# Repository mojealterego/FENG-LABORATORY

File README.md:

# FENG-LABORATORY — Thermo-IoT

**OCHRONA WYNALAZKU:** Repozytorium jest **publiczne**, a wcześniejsze commity mogą stanowić ujawnienie stanu techniki. Copyright ani dopisek „All rights reserved” **nie zastępuje zgłoszenia patentowego**. Nie publikować nowych unikatowych rozwiązań konstrukcyjnych przed przeglądem przez rzecznika patentowego. [Procedura IP](docs/IP_PROTECTION_PL.md) · [Rejestr dat publicznych ujawnień](docs/IP_PUBLIC_DISCLOSURE_REGISTER.md).

**Prawa autorskie i kontakt:** © 2026 **Mojeaterego — Andrzej Mikulski**. **Wszelkie prawa zastrzeżone / All rights reserved.** E-mail: **mojealterego21@gmail.com** · tel. **+48 455 575 337**. Szczegóły: [LICENSE](LICENSE).

Repozytorium rozwojowe projektu **Thermo-IoT** w kontekście FENG 2.27 „Laboratorium Innowatora”.

**Stan na 9 października 2026:** zweryfikowany kod referencyjny, testy i dokumentacja koncepcyjna. **Brak potwierdzonego prototypu, eksperymentów metrologicznych i poziomu TRL.** Ani dostęp do programu, ani dofinansowanie nie są zagwarantowane.

## Dostarczone podsystemy

| Moduł | Zakres | Czego nie dowodzi |
|---|---|---|
| `thermo_iot.energy` | energia superkondensatora, bilans mocy netto, limit duty cycle | mocy na konkretnej rurze |
| `thermo_iot.scheduler` | interwał pomiarowy, rezerwa i ograniczenia mocy | szczytowego prądu TX i cold start |
| `thermo_iot.telemetry` | wersjonowany protokół 8 B, parser TTN v3, idempotentna baza SQLite | pracy LoRaWAN na urządzeniu |
| `thermo_iot.gateway` | offline ingest / report, lokalny webhook z tokenem | bezpiecznej publicznej usługi produkcyjnej |
| `thermo_iot.anomaly` | odporna statystyka odchyleń temperatury | wykrycia wycieków i błędów procesowych |
| `thermo_iot.lab` | analiza pomiarów I–V/TEG z jawnie oznaczonym źródłem danych | kalibracji i jakości pomiarów |
| `firmware/` | przenośny kodek C11 testowany z Pythonem | kompletnego firmware, PCB i modemu |

## Uruchomienie (Python 3.10+ / C11)

```bash
python -m unittest discover -s tests -v
python -m thermo_iot --teg-mw 0.1 --efficiency 0.65 --sleep-uw 8 --cycle-mj 21.9
python -m thermo_iot.gateway ingest --db local-telemetry.sqlite --file examples/ttn_v3_uplink.json
python -m thermo_iot.gateway report --db local-telemetry.sqlite --app district-heat --device pipe-1
python -m thermo_iot.lab --file examples/synthetic_teg_sweep.csv
cc -std=c11 -Wall -Wextra -Werror -pedantic -Ifirmware/include firmware/src/thermo_iot_frame.c firmware/tests/test_frame.c -o /tmp/thermo-iot-frame-tests
/tmp/thermo-iot-frame-tests
```

**Ostrzeżenie: przyklad --cycle-mj 21.9 nie jest zweryfikowaną energią cyklu LoRaWAN.** Wyłącznie ilustracyjny impuls 87 mA x 200 ms przy 3,3 V pobiera ponad 57 mJ przed oknami RX i stratami. PCB ma tylko C6=470 uF na VOUT, co stanowi elektryczny HOLD/NO-GO dla referencyjnego profilu. Symulowane 2,5 F nie istnieje na tej szynie, a VSTORE 5,25 V nie wolno podłączać bezpośrednio do STM32WLE. Analizy: [power_gate](thermo_iot/power_gate.py), [harvester_rail](thermo_iot/harvester_rail.py) i [protokół](docs/RF_POWER_BROWNOUT_HOLD.md). Nie są to pomiary fizyczne.

**Uwaga:** w plikach przykładowych występują wyłącznie **syntetyczne** dane przeznaczone do demonstracji formatu. Lokalny webhook wymaga tokenu i nie jest wystawiany domyślnie poza localhost. Zob. [protokół IoT](docs/PROTOKOL_IOT.md).

## Demonstrator panelu telemetrii (lokalnie)

```bash
python -m thermo_iot.demo --db ./thermo-synthetic-demo.sqlite --count 144
python -m thermo_iot.dashboard --db ./thermo-synthetic-demo.sqlite --port 8766
```

Otwórz `http://127.0.0.1:8766/` na komputerze, na którym działa Python. Dane są **wygenerowane syntetycznie** i zapisywane wyłącznie do nowo utworzonej bazy; skrypt odmawia nadpisania istniejącej bazy. Panel nie pozwala na sterowanie instalacją ani jej urządzeniami. [Opis dashboardu](docs/DASHBOARD.md).

## Baza dokumentacji

- [Karta robocza do wniosku IPB](docs/WNIOSEK_THERMO_IOT.md)
- [Audyt twierdzeń i ryzyk](docs/AUDYT_TWIERDZEN.md)
- [Plan walidacji i progi GO/NO-GO](docs/PLAN_WALIDACJI.md)
- [Model biznesowy i walidacja klientów](docs/MODEL_BIZNESOWY.md)
- [Źródła formalne i naukowe](docs/ZRODLA.md)
- [Architektura MVP](docs/ARCHITEKTURA_MVP.md)
- [Protokół telemetrii / TTN](docs/PROTOKOL_IOT.md)
- [Zasady oceny analityki](docs/ANALITYKA.md)
- [Protokół metrologii TEG i analizy CSV](docs/METROLOGIA_TEG.md)
- [Analiza konkurencji i wcześniejszego stanu techniki](docs/PRIOR_ART_I_WYROZNIK.md)
- [Lista kontrolna gotowości zgłoszenia](docs/GOTOWOSC_ZGLOSZENIA.md)
- [Harmonogram 12 tygodni](docs/HARMONOGRAM_12_TYGODNI.md)
- [BOM funkcjonalny i wymagania techniczne](docs/BOM_I_WYMAGANIA_TECHNICZNE.md)
- [Przegląd kandydatów PMIC/MCU/sensora i ryzyk rozruchu](docs/HARDWARE_PRELIMINARY.md)
- [Energia z profilu czasowego generatora](docs/TRACE_SIMULATION.md)
- [Firmware: histereza i bramka mocy](docs/FIRMWARE_POWER_POLICY.md)
- [Granice bezpieczeństwa IT/OT](SECURITY.md)

## Faza HW / Firmware / Walidacja LoRaWAN (2026-10-09)

**Implementacje repozytoryjne są przeznaczone do prób laboratoryjnych — brak dowodu fizycznej integracji.** Zobacz [macierz stanu dowodowego](docs/STATUS_HARDWARE_TESTS.md).

- [KiCad — schemat i PCB pasywnego adaptera stanowiska](hardware/kicad/) (nie jest finalną płytą PMIC/MCU ani wydanym Gerberem).
- [STM32WLE5JC — aplikacja C11 i wymagany adapter CubeWL](docs/STM32WLE5_FIRMWARE.md) (laboratoryjny ELF/HEX z GNU ARM GCC dostępny z CI; niewgrany do fizycznego MCU).
- [Wio-E5: sprzętowy test jednej transmisji i weryfikacja odczytu TTN](docs/TEST_LORAWAN_REAL.md) (wymaga rzeczywistego urządzenia).
- [TEG i PMIC — akwizycja SCPI oraz metrologia](docs/TEG_PMIC_CAPTURE.md) (bez pomiarów rzeczywistych w repo).

Przykładowy test kontrolny portu, **bez emisji**:

```bash
python -m pip install pyserial
python -m thermo_iot.lorawan_fieldtest --port COM3
```

Pojedynczy test fizycznego nadawania (tylko po skonfigurowaniu OTAA/anteny i sprawdzeniu lokalnych wymogów radiowych):

```bash
python -m thermo_iot.lorawan_fieldtest --port COM3 --send --temperature-centic 4300 --capacitor-mv 3000
```

COM3 jest tylko przykładem Windows i musi zostać zastąpiony faktycznym portem. Liczby w tym teście są wpisywane przez operatora; nie dowodzą pracy czujnika. Odbiór należy oddzielnie potwierdzić w The Things Stack.

## Projekt aktywnego harvester'a i ścieżka weryfikacji fizycznej — październik 2026

**Nowe elementy przeznaczone do rzeczywistej budowy demonstratora:**

- [LTC3108GN16 — schemat aktywnego PMIC i projekt PCB w KiCad](hardware/active_power/) — PCB **częściowo trasowana: 2 nets połączone, 28 pozycji nadal niepołączonych**, status produkcyjny HOLD; transformator 1:100 poza płytką.
- [Natywny overlay STM32CubeIDE dla STM32WLE5JC / Wio-E5](firmware/stm32wle5jc/README.md) — generator 4 plików integrowanych z oficjalnym Seeed LoRaWAN End Node; **zbudowano ELF/HEX dla profilu laboratoryjnego; brak flash urządzenia**.
- [Pobieranie rzeczywistych parametrów PMIC z pięciu przyrządów SCPI](thermo_iot/pmic.py) — wejście, wyjście, VSTORE, próba cold-start (wymaga własnej aparatury).
- [Próba radiowa Wio-E5 EU868 i weryfikacja odczytu TTN](thermo_iot/lorawan_fieldtest.py) — program istnieje, **brak rzeczywistego raportu odbioru**.
- [Aktualna macierz GO/NO-GO dla sprzętowego MVP](docs/STATUS_HARDWARE_TESTS.md).

**Uwaga:** bit 7 ramki LoRaWAN (0x80) oznacza laboratoryjny odczyt temperatury wewnętrznej MCU. Backend przechowuje te rekordy jako `reference_telemetry` i **wyklucza je z wykrywania anomalii rurociągu**. Nie wolno przedstawiać ich jako pomiaru rury lub wycieku.

## Kamień milowy: pełny build referencyjnego firmware STM32WLE5JCIx

**Weryfikacja 9.10.2026:** w GitHub Actions rzeczywiście skompilowano i zlinkowano natywny obraz **ELF/Intel HEX**, ze startup i linker script producenta Seeed, na `arm-none-eabi-gcc`. Dane kompilacji: **63 564 B FLASH (24,25% z 256 KiB)**, **8 068 B BSS** i **228 B DATA**. SHA-256 HEX: `e9a3d1df50e8c5a0eb3a52d03a78ce236c72ead47e3924e0c9d1b1b63d66a4ea`.

[GitHub Actions: udany pełny build ELF/HEX](https://github.com/mojealterego/FENG-LABORATORY/actions/runs/37956017016) · [archiwum ELF/HEX/MAP](https://github.com/mojealterego/FENG-LABORATORY/actions/runs/37956017016/artifacts/11627633166) · [skrypt kompilacji](firmware/stm32wle5jc/build_cube_gcc.py).

**Granica dowodowa:** jest to kompletna kompilacja **referencyjnego firmware LoRaWAN RF** (temperatura krzemu STM32, ręcznie brak TEG/supercap), a **nie docelowy pełny firmware bezbateryjnego czujnika rury**. Nie nastąpiło programowanie układu SWD, OTAA w środowisku fizycznym, pomiar TX ani odbiór w TTN.

## Ocena jakości uplinków LoRaWAN — tylko analiza lokalnego eksportu TTN

Nowy moduł [`thermo_iot.rf_audit`](docs/RF_FIELD_AUDIT.md) weryfikuje plik JSONL z faktycznie wyeksportowanymi (przez operatora) zdarzeniami The Things Stack v3. Zlicza unikatowe ramki, ponowne dostarczenia, zmiany sesji, nieciągłości FCnt i dostępne RSSI/SNR; izoluje laboratoryjne ramki 0x80 od danych czujnika rury. **Nie wylicza „procentu dostarczonych pakietów” z samych odebranych ramek**, ponieważ nie znamy wszystkich prób nadawania.

```bash
python -m thermo_iot.rf_audit --file private/mvp-evidence/ttn-uplinks.jsonl \
  --app-id thermo-lab --device-id pipe-1
```

Plik JSONL ma być zachowany wyłącznie lokalnie/prywatnie, bez tokenów, kluczy ani nieujawnionych rozwiązań patentowych. Analiza samego eksportu nie poświadcza, że użytkownik przeprowadził transmisje.

## Prywatne dowody fizycznego MVP (poza GitHub)

Moduł `thermo_iot.mvp_acceptance` analizuje w **prywatnym katalogu** kompletność, SHA-256 i spójność 7 typów dokumentów: TEG I-V, PMIC cold-start, raport z UART, niezależny uplink TTN, wynik DRC **aktywnego** PCB, log flash MCU i zapis 7 dni pracy energetycznej. **Nie nadaje automatycznie statusu „fizyczne MVP wykonane”.**

```bash
python -m thermo_iot.mvp_acceptance --root private/mvp-evidence --create-manifest
python -m thermo_iot.mvp_acceptance --root private/mvp-evidence
```

Wymaga **wcześniej faktycznie wykonanych pomiarów i zdarzeń**; nie generuje fałszywych danych. [Procedura i kryteria](docs/MVP_EVIDENCE_PRIVATE.md). Ścieżka `private/` jest ignorowana przez Git i blokowana przez lokalne hooki przed publikacją.

## Krytyczny warunek zasilania impulsowego LoRaWAN

W publicznym projekcie LTC3108 zamontowany kondensator C6 = **470 µF** stanowi **elektryczny NO-GO** dla przyjętego profilu 87 mA przez 200 ms, nawet z optymistycznym 4,5 mA wsparciem PMIC. Referencyjne wyliczenie pierwszego rzędu wskazuje minimum ~**13,1 mF** bez zapasu temperaturowego/tolerancji. Zasilenie STM32 bezpośrednio z VSTORE ~5,25 V jest niedopuszczalne. [Szczegółowa analiza](docs/RF_POWER_BROWNOUT_HOLD.md). To wynik symulacji, nie pomiar. Aktywna PCB i fizyczne MVP pozostają **HOLD**.

## Warunki przed zgłoszeniem

Wymagane są potwierdzone dane pomysłodawców, właścicieli praw IP, zasoby, kompetencje, oświadczenia formalne i oryginalny formularz operatora. Kod i wyniki symulacji nie mogą zastępować protokołów zbudowania i walidacji urządzenia.

Zalecana kolejność: **pomiar TEG → bilans energetyczny/PMIC → podzespoły i prototyp → telemetryka terenowa → zbiór zdarzeń → model predykcyjny → biznes/SLA**.

Prace prowadzone w gałęzi `main`, testowane automatycznie przez GitHub Actions.

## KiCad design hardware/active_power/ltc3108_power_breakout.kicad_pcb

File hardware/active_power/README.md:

# Active Thermo-IoT harvester PCB candidate A0 (LTC3108GN16)

## Important status

This folder contains **native KiCad schematic/net-assigned PCB for an LTC3108 active power breakout**, not a finalized complete industrial IoT device. The PCB has placed parts, assigned nets, and **two explicitly routed charge-pump connections** (C1.2→U1.13, C2.2→U1.14); the remainder is still UNROUTED. Real KiCad 10 automated ERC/DRC has been RUN, but **blocking warnings and unconnected copper remain**; there is no passed manufacturing signoff, mechanical clearance/assembly validation, or hot/cold-start test. **Do NOT send to PCB fabrication as is.**

The design uses the **LTC3108EGN** 16-pin SSOP package and an **external transformer** for ease of bench swapping. Pin numbering matches the manufacturer GN16 top-view drawing (Rev D). Manufacturer typical application: https://www.analog.com/media/en/technical-documentation/data-sheets/3108fc.pdf.

## Architecture and rationale

J1 TEG source -> C5 reservoir + primary of external 1:100 transformer (J2 primary TEG_P to SW). Secondary ground/Sec_HI -> C1 1nF and C2 330pF -> LTC3108's C1/C2 charge pump. VS1=VAUX and VS2=GND selects **3.3V** VOUT. C3 1uF VAUX, C4 2.2uF VLDO. J3 exposes VOUT with C6 470uF. J4 exposes 5V VSTORE for an external 0.1F / 6.3V energy reservoir (C7 DNP). J5 exposes PGD for a **high-impedance** diagnostic probe. VOUT2_EN tied to GND, VOUT2 unused.

**Critical:** J2 four-pin 2.54mm transformer breakout does not correspond to the transformer manufacturer's surface-mount pad numbering. Confirm coil polarity/pinout and orientation on the real LPR6235 before assembly; no transformer is soldered on this PCB.

| IC pin | Function | Circuit net |
|---|---|---|
| 1, 8, 9, 16 | GND | GND |
| 2 | VAUX | VAUX |
| 3 | VSTORE | VSTORE |
| 4 | VOUT | VOUT |
| 5 | VOUT2 | NC_VOUT2 / unconnected |
| 6 | VLDO | VLDO |
| 7 | PGD | PGD |
| 10 | VS2 | GND |
| 11 | VS1 | VAUX |
| 12 | VOUT2_EN | GND |
| 13 | C1 | PMIC_C1 |
| 14 | C2 | PMIC_C2 |
| 15 | SW | SW |

## Stop/go constraints

* **Minimum 20mV** LTC3108 startup is datasheet input voltage under a 1:100 transformer, NOT a claim about any particular TEG, output current, zero gradient or autonomous 87mA radio peaks.
* LTC3108 VOUT current limit from datasheet ~2.8–7.5 mA (typ ~4.5mA), far below potential LoRa high-power pulses; **supply RF from measured reservoir energy**, and implement supervised power gating, hold-up / ESR tests, and output supply-current limits.
* VSTORE operates at about 5 V, **not acceptable as direct STM32WLE supply**. Connect MCU only to verified VOUT 3.3 V rail (and review startup/sag).
* The selected capacitor footprints / dimensions are *placeholders*, not approved mechanical data. Choose actual vendor MPNs, tolerances, lead pitch, ESR and leakage, and recalculate hold-up before routing.
* Avoid connecting J1 to live district heating conductors, mains, or unqualified hot surfaces. All measurements must be done on a controlled isolated low-voltage thermal rig.

## Required remaining manufacturing gates

1. Exact BOM manufacturers, cap lead pitch, Coilcraft winding pin mapping, safe VS1 selection and TEG voltage/current envelope verified.
2. KiCad opens schematic and PCB and reports **zero blocking ERC/DRC**, zero unconnected nets after a proper manual route, correct pad/net parity, mask clearance and track capacity.
3. Independent review of thermal, electrical and RF wiring and source mechanical drawings.
4. Gerber + Excellon drill exports and independent preview; then limited prototype fabrication with current-limited bench bring-up.
5. Cold-start, brownout, leakage, ESR and peak TX/RX validation. No claims of measured performance until archived data exists.

## Footprint source library

The local `ThermoActive.pretty/` directory and `fp-lib-table` resolve the custom SMD/TH footprints used in the schematic. They are **engineering placeholders**, not manufacturer-validated land patterns. In particular, `RadialCap` stands for an unselected 2.54mm-pitch THT cap and can be dangerous if a larger diameter, different polarity, clearance or thermal derating is required. The SSOP16 land-pattern is provisional and must be compared with Analog Devices GN16 recommended solder pattern before release.

## Routing progress — 9 Oct 2026 (A0 candidate; NOT FOR FAB)

The **manufacturer-reference** capacitor-to-LTC3108 nets `PMIC_C1` and `PMIC_C2` have now been laid on F.Cu at 0.20 mm nominal width. The real KiCad 10.0.6 DRC diagnostics [37960523837](https://github.com/mojealterego/FENG-LABORATORY/actions/runs/37960523837) report **28 unconnected pads remaining**, down from 30, and **13 existing footprint-library mismatch warnings**. There were no new inter-track violations reported for the two routed nets. These are preliminary reference-board traces, **not an undisclosed novel circuit**. Transformer pin order, capacitor land-patterns, ESR, clearance, and all other wiring remain HOLD; the board shall not be manufactured or attached to live heating infrastructure without independent electrical/DFM validation.

`hardware/cad_gate.py` interprets KiCad textual DRC to machine-readable `HOLD` / `ENGINEERING_REVIEW_REQUIRED`. Even a hypothetical zero-violation DRC result never sets `fabrication_authorized` to true — a human review is mandatory.

## Explicit RF supply brownout blocker (electrical engineering HOLD)

The open C6 = **470 µF at VOUT 3.3 V** is not sufficient as the sole storage capacitor for the **illustrative** 87 mA / 200 ms STM32WLE transmit pulse even under the optimistic constant LTC3108 VOUT current assumption. A charge/ESR first-order model suggests at least **13.1 mF** for the specified illustrative pulse and minimum voltage, before derating and protection margins. This number is **NOT** a production capacitor selection or a validated performance value. VSTORE (nominally around 5 V) must never be directly connected to STM32WLE VDD. Independent current transient measurement and a suitable qualified power architecture remain prerequisites.

See [reproducible power-integrity analysis](../../docs/RF_POWER_BROWNOUT_HOLD.md) and `python -m thermo_iot.harvester_rail`. Engineering status remains **HOLD** even if routing progress reduces unconnected pads.

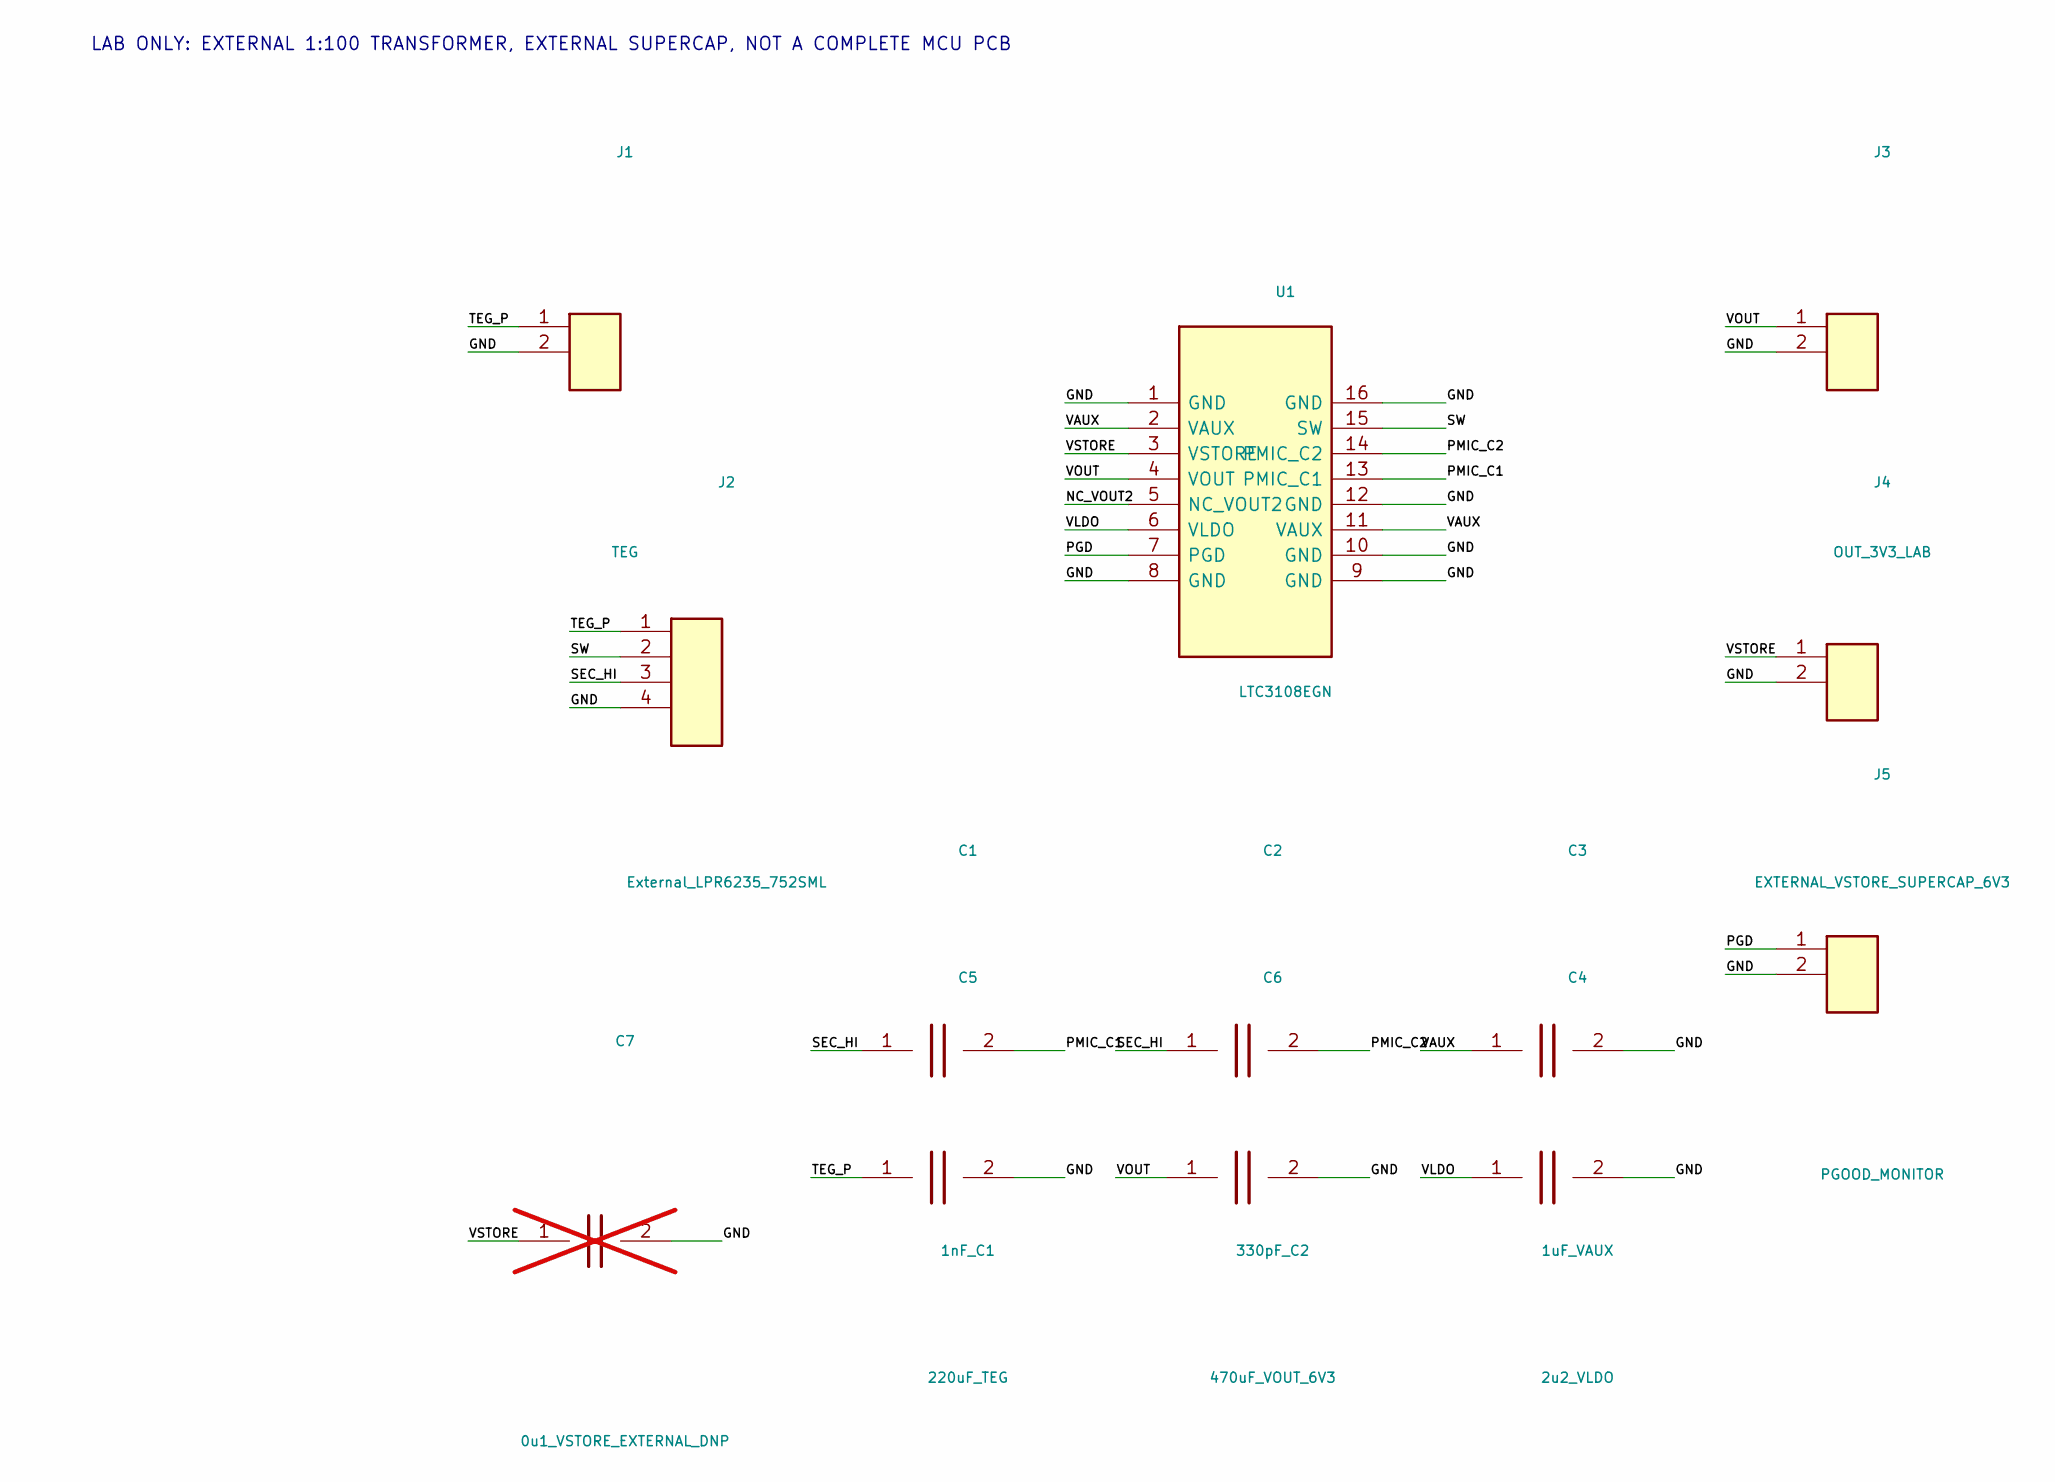
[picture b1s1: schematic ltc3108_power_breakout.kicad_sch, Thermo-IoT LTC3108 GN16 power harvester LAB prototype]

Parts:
C1: 1nF_C1; Cap0805
C2: 330pF_C2; Cap0805
C3: 1uF_VAUX; Cap0805
C4: 2u2_VLDO; Cap0805
C5: 220uF_TEG; RadialCap
C6: 470uF_VOUT_6V3; RadialCap
C7: 0u1_VSTORE_EXTERNAL_DNP; RadialCap; not fitted
J1: TEG; Header1x2
J2: External_LPR6235_752SML; Header1x4
J3: OUT_3V3_LAB; Header1x2
J4: EXTERNAL_VSTORE_SUPERCAP_6V3; Header1x2
J5: PGOOD_MONITOR; Header1x2
U1: LTC3108EGN; SSOP16_P0635

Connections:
GND: C3.2, C4.2, C5.2, C6.2, C7.2, J1.2, J2.4, J3.2, J4.2, J5.2, U1.1 (GND), U1.8 (GND), U1.9 (GND), U1.10 (GND), U1.12 (GND), U1.16 (GND)
NC_VOUT2: U1.5 (NC_VOUT2)
PGD: J5.1, U1.7 (PGD)
PMIC_C1: C1.2, U1.13 (PMIC_C1)
PMIC_C2: C2.2, U1.14 (PMIC_C2)
SEC_HI: C1.1, C2.1, J2.3
SW: J2.2, U1.15 (SW)
TEG_P: C5.1, J1.1, J2.1
VAUX: C3.1, U1.2 (VAUX), U1.11 (VAUX)
VLDO: C4.1, U1.6 (VLDO)
VOUT: C6.1, J3.1, U1.4 (VOUT)
VSTORE: C7.1, J4.1, U1.3 (VSTORE)

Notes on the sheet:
LAB ONLY: EXTERNAL 1:100 TRANSFORMER, EXTERNAL SUPERCAP, NOT A COMPLETE MCU PCB

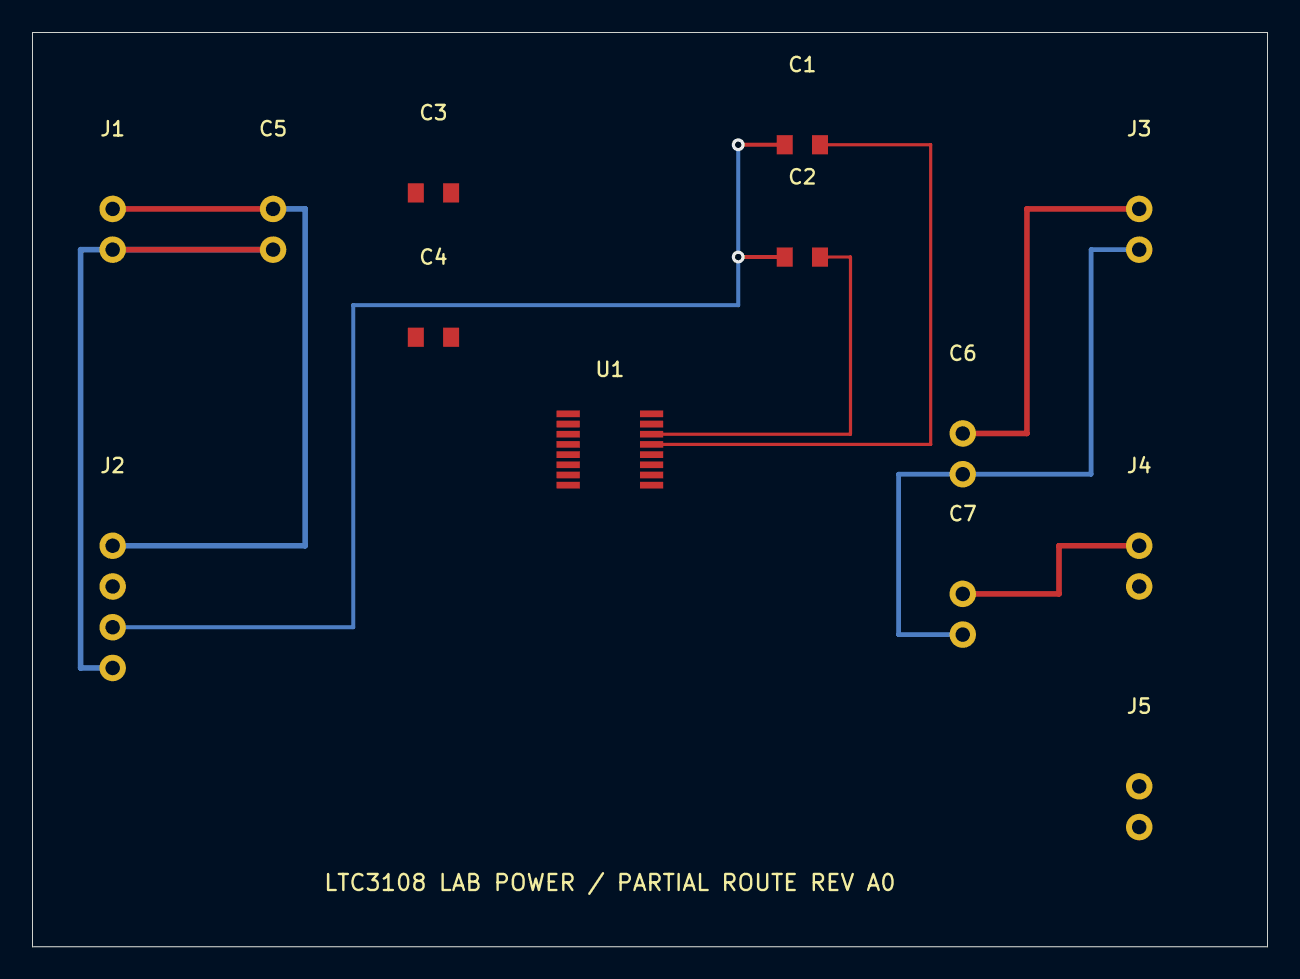
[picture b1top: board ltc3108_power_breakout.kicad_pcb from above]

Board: 2 copper layers, 77.0 x 57.0 mm, 13 parts (0 on the bottom side), 11 nets.

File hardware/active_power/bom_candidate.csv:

Ref,Component,Value/Specification,Footprint,Notes
U1,LTC3108EGN,LTC3108 SSOP16 GN,ThermoActive:SSOP16_P0635,Manufacturer pinout Rev D verify before assembly
C1,Ceramic,1nF >=10V,ThermoActive:Cap0805,C1 coupling
C2,Ceramic,330pF >=16V,ThermoActive:Cap0805,C2 coupling
C3,Ceramic,1uF >=6.3V,ThermoActive:Cap0805,VAUX decoupling
C4,Ceramic,2.2uF >=6.3V,ThermoActive:Cap0805,VLDO decoupling
C5,Polarized input reservoir,220uF low leakage >=6.3V,ThermoActive:RadialCap,Verify leakage and actual lead pitch
C6,Polarized regulated output,470uF >=6.3V low ESR,ThermoActive:RadialCap,Check ripple and pulses
C7,DNP optional VSTORE,DNP,ThermoActive:RadialCap,External supercap on J4 instead
J1,TEG terminal,2-pin 2.54mm,ThermoActive:Header1x2,TEG_P and GND
J2,External transformer connector,4-pin 2.54mm,ThermoActive:Header1x4,Winding polarity requires verification with Coilcraft
J3,Output 3.3V terminal,2-pin 2.54mm,ThermoActive:Header1x2,Do not attach MCU until safe load profiling
J4,External 0.1F 6.3V supercap,2-pin 2.54mm,ThermoActive:Header1x2,Check ESR leakage polarity max ratings
J5,PGOOD monitor,2-pin 2.54mm,ThermoActive:Header1x2,High impedance meter only
T1,Transformer external,Coilcraft LPR6235-752SML 1:100,NOT ON PCB,Needs physical breakout and winding verification

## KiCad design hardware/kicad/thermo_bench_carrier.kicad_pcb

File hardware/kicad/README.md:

# Thermo-IoT Bench Carrier A0 — native KiCad sources

**Funkcja:** pasywna, dwuwarstwowa płytka *stanowiska laboratoryjnego*, nie docelowy system bezbateryjny i nie płytka z układem LTC3108. Służy do podłączenia zewnętrznie zasilanej płytki Wio-E5, UART USB (3,3 V), toru pomiarowego surowego TEG i oddzielnego pomiaru PMIC.

## Złącza (pad nr 1 wyznacza pad prostokątny)

| Ref | Pad | Net | Cel |
|---|---|---|---|
| J1 | 1,2 | `+3V3_EXT`, `GND` | **tylko laboratoryjny** regulowany zasilacz 3,3 V, ograniczenie prądu |
| J2 | 1..4 | `+3V3_EXT`, `GND`, `MCU_TX`, `MCU_RX` | interfejs Wio-E5 Dev Board (sprawdzić ręcznie pinout przed podłączeniem) |
| J3 | 1..3 | `GND`, `MCU_RX`, `MCU_TX` | konwerter USB-UART logic 3,3 V; RX adaptera -> J2.3, TX -> J2.4 |
| J4 | 1,2 | `TEG_P`, `TEG_N` | wyłącznie pomiar TEG, brak połączenia z obwodami zasilania |
| J5 | 1,2 | `PMIC_VOUT`, `PMIC_RETURN` | wyłącznie pomiar PMIC, brak połączenia z Wio-E5 i J1 |

**OSTRZEŻENIE:** Nie wolno bezpośrednio łączyć 5 V VSTORE LTC3108, jego 2,2 V wyjścia LDO albo niestabilnego napięcia z TEG z pinami MCU. Płytka nie zawiera ogranicznika przepięć, bezpiecznika ani regulatora. Traktować ją jako **przyrząd laboratoryjny do niskich napięć** i zasilać J1 z zabezpieczonego zasilacza 3,3 V; nie instalować na pracującej instalacji przemysłowej.

## Pliki

- `thermo_bench_carrier.kicad_sch`: schemat z 5 złączami i identycznymi nazwami nets.
- `thermo_bench_carrier.kicad_pcb`: dwuwarstwowa PCB z trasami tylko dla zasilania UART+3.3 V/GND, TEG i PMIC są **osobnymi, niepołączonymi parzystymi złączami pomiarowymi**.
- `ThermoBench.pretty/`: wbudowane źródła footprintów 1×2, 1×3, 1×4, raster 2,54 mm.
- `fp-lib-table`: lokalna biblioteka footprintów.

Płytka ma **70 × 44 mm** (obrys x=12..82; y=13..57), przewierty padów 1,0 mm. Przed zamówieniem PCB wymaga weryfikacji w **KiCad ERC/DRC, orientacji pinów, tolerancji mechanicznych i przeglądu DFM**. To nie jest produkcyjnie zweryfikowany Gerber — w repo nie ma autoryzowanego testu sprzętowego ani walidacji EDA.

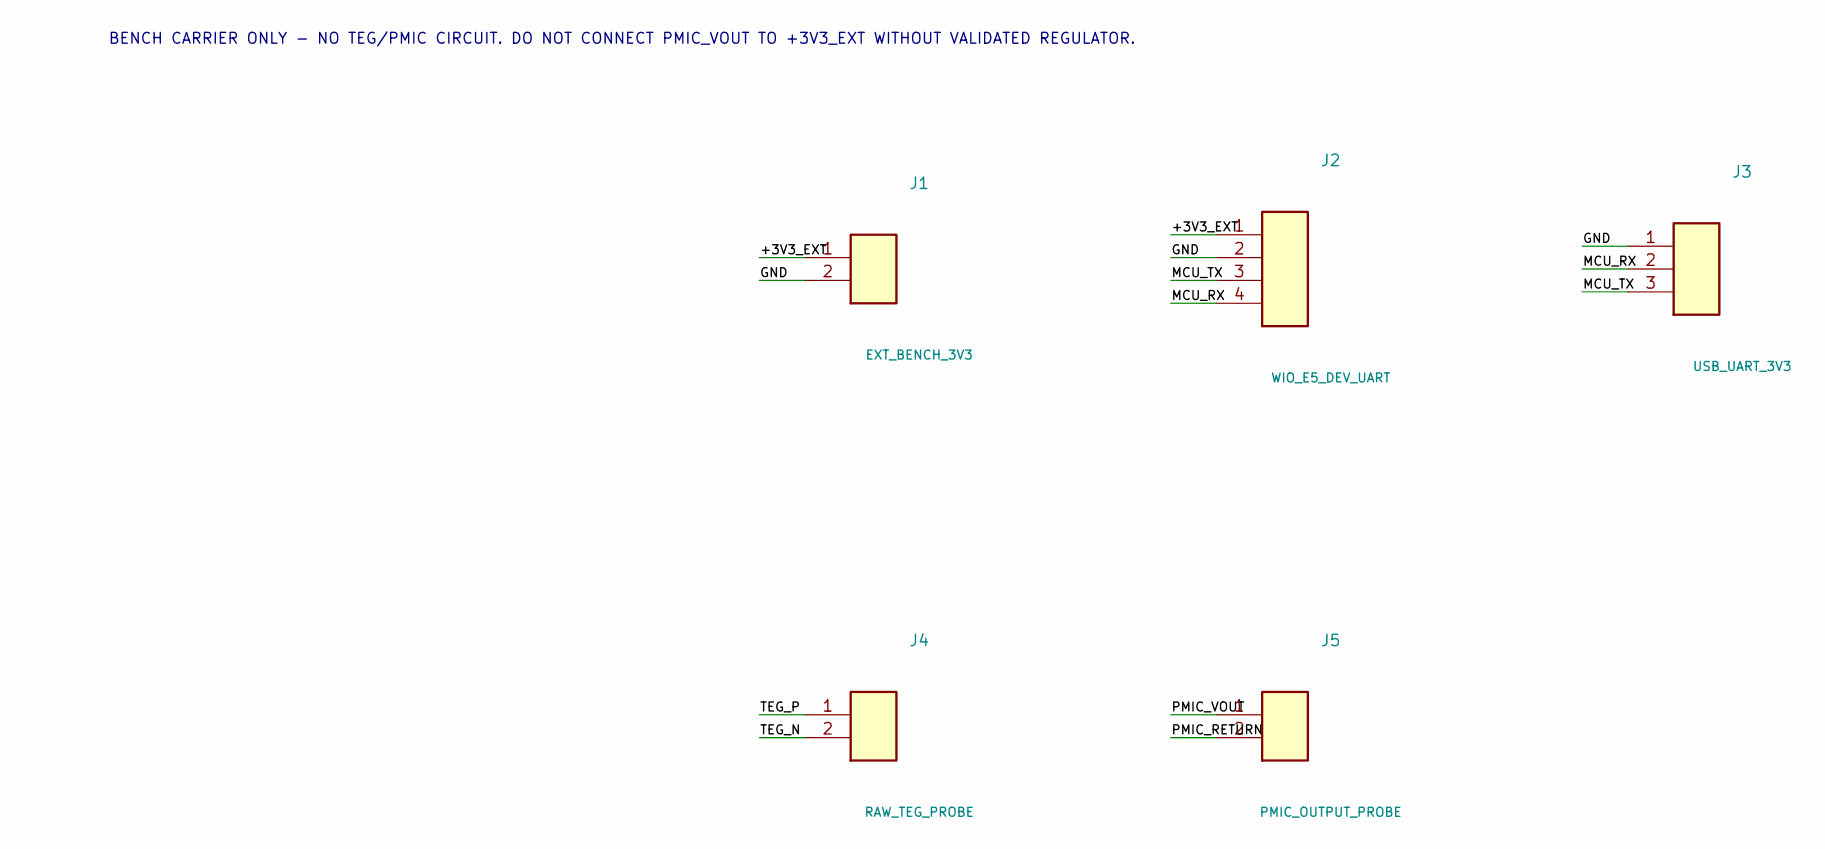
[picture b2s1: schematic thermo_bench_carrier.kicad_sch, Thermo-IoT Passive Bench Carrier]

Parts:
J1: EXT_BENCH_3V3; BenchConn_01x02
J2: WIO_E5_DEV_UART; BenchConn_01x04
J3: USB_UART_3V3; BenchConn_01x03
J4: RAW_TEG_PROBE; BenchConn_01x02
J5: PMIC_OUTPUT_PROBE; BenchConn_01x02

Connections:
+3V3_EXT: J1.1 (PIN_1), J2.1 (PIN_1)
GND: J1.2 (PIN_2), J2.2 (PIN_2), J3.1 (PIN_1)
MCU_RX: J2.4 (PIN_4), J3.2 (PIN_2)
MCU_TX: J2.3 (PIN_3), J3.3 (PIN_3)
PMIC_RETURN: J5.2 (PIN_2)
PMIC_VOUT: J5.1 (PIN_1)
TEG_N: J4.2 (PIN_2)
TEG_P: J4.1 (PIN_1)

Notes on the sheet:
BENCH CARRIER ONLY - NO TEG/PMIC CIRCUIT. DO NOT CONNECT PMIC_VOUT TO +3V3_EXT WITHOUT VALIDATED REGULATOR.

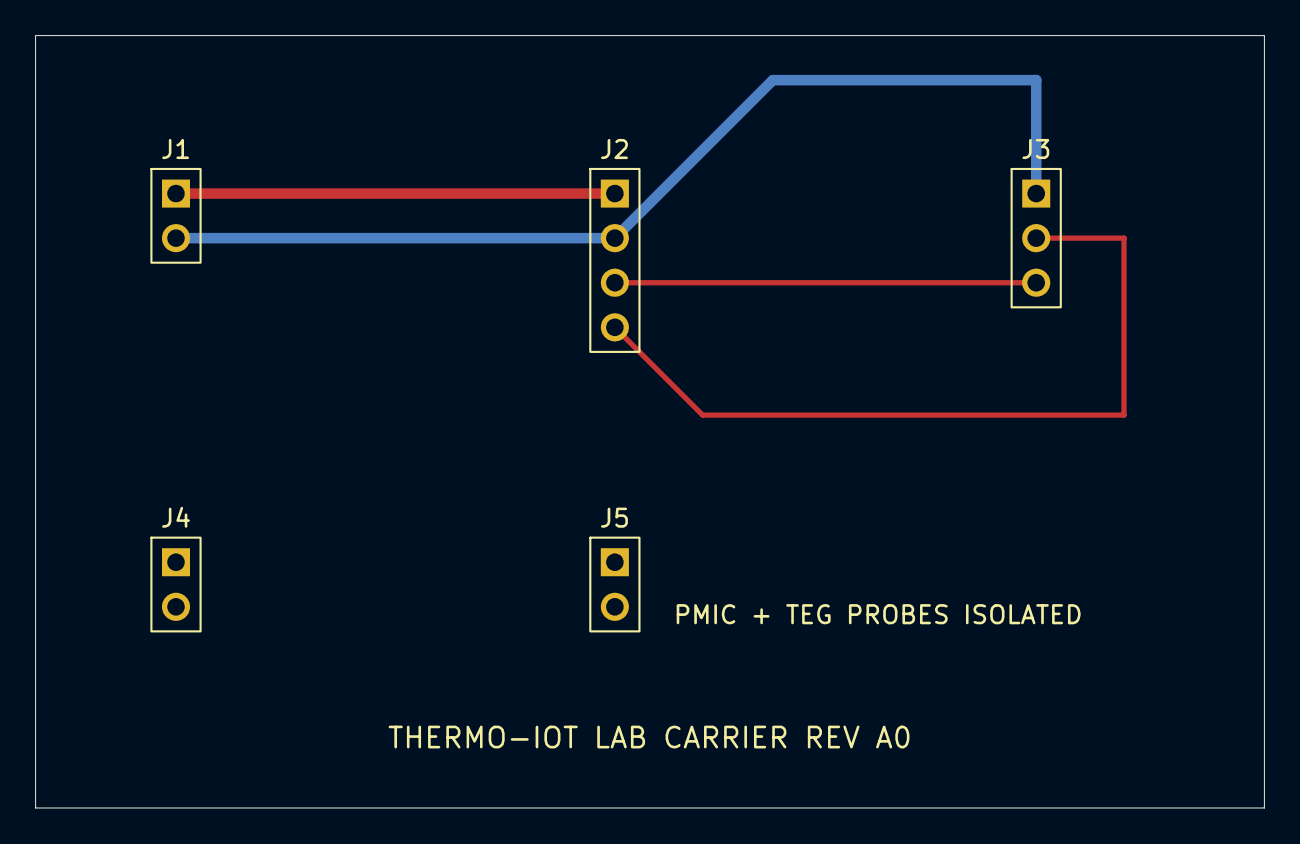
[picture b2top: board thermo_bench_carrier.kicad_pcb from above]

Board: 2 copper layers, 70.0 x 44.0 mm, 5 parts (0 on the bottom side), 4 nets.

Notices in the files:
hardware/active_power/ltc3108_power_breakout.kicad_pcb:
MOJEATEREGO (C) 2026 A. MIKULSKI
